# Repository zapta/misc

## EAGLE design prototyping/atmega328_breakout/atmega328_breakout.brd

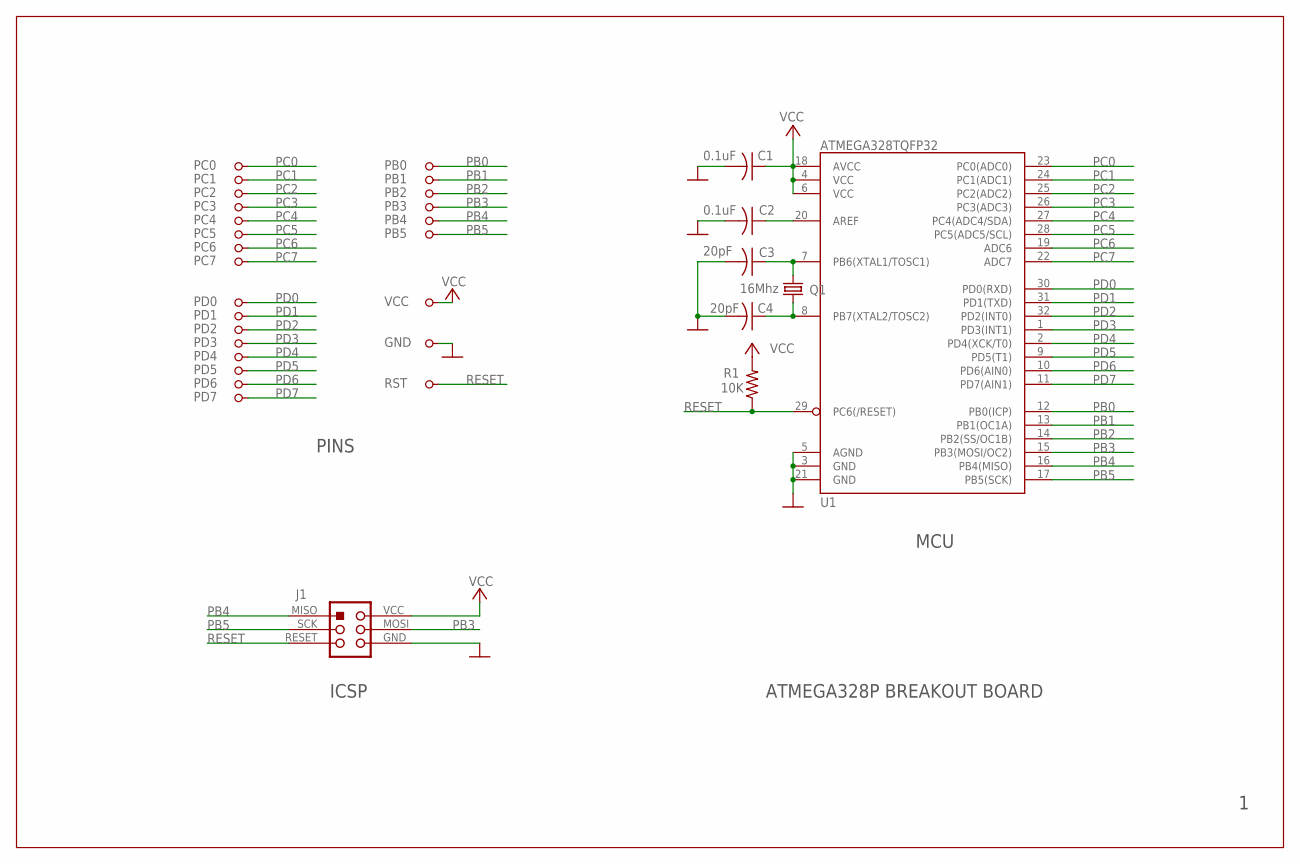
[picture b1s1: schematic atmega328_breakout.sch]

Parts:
C1, C2: 0.1uF; C0603
C3, C4: 20pF; C0603
GND: PINHD-1X1; 1X01
J1: ICSP
PB0, PB1, PB2, PB3, PB4, PB5: PINHD-1X1; 1X01
PC0, PC1, PC2, PC3, PC4, PC5, PC6, PC7: PINHD-1X1; 1X01
PD0, PD1, PD2, PD3, PD4, PD5, PD6, PD7: PINHD-1X1; 1X01
Q1: 16Mhz; CRYSTAL-CTS406
R1: 10K; R0603
RST: PINHD-1X1; 1X01
U1: ATMEGA328TQFP32; TQFP32-08
VCC: PINHD-1X1; 1X01

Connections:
AREF: C2.1, U1.20 (AREF)
GND: C1.2, C2.2, C3.2, C4.2, GND.1, J1.GND, U1.3 (GND), U1.5 (AGND), U1.21 (GND)
unnamed: C3.1, Q1.1, U1.7 (PB6(XTAL1/TOSC1))
unnamed: C4.1, Q1.3 (2), U1.8 (PB7(XTAL2/TOSC2))
PB0: PB0.1, U1.12 (PB0(ICP))
PB1: PB1.1, U1.13 (PB1(OC1A))
PB2: PB2.1, U1.14 (PB2(SS/OC1B))
PB3: J1.MOSI, PB3.1, U1.15 (PB3(MOSI/OC2))
PB4: J1.MISO, PB4.1, U1.16 (PB4(MISO))
PB5: J1.SCK, PB5.1, U1.17 (PB5(SCK))
PC0: PC0.1, U1.23 (PC0(ADC0))
PC1: PC1.1, U1.24 (PC1(ADC1))
PC2: PC2.1, U1.25 (PC2(ADC2))
PC3: PC3.1, U1.26 (PC3(ADC3))
PC4: PC4.1, U1.27 (PC4(ADC4/SDA))
PC5: PC5.1, U1.28 (PC5(ADC5/SCL))
PC6: PC6.1, U1.19 (ADC6)
PC7: PC7.1, U1.22 (ADC7)
PD0: PD0.1, U1.30 (PD0(RXD))
PD1: PD1.1, U1.31 (PD1(TXD))
PD2: PD2.1, U1.32 (PD2(INT0))
PD3: PD3.1, U1.1 (PD3(INT1))
PD4: PD4.1, U1.2 (PD4(XCK/T0))
PD5: PD5.1, U1.9 (PD5(T1))
PD6: PD6.1, U1.10 (PD6(AIN0))
PD7: PD7.1, U1.11 (PD7(AIN1))
RESET: J1.RESET, R1.1, RST.1, U1.29 (PC6(/RESET))
VCC: C1.1, J1.VCC, R1.2, U1.4 (VCC), U1.6 (VCC), U1.18 (AVCC), VCC.1

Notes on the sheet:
ATMEGA328P BREAKOUT BOARD
ICSP
PINS
MCU

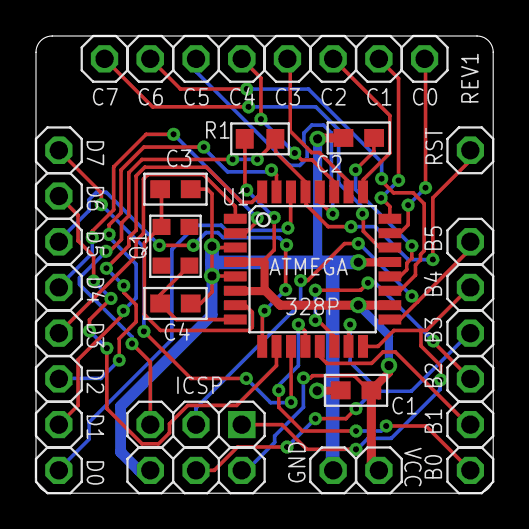
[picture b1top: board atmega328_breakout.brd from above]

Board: 2 copper layers, 25.4 x 25.4 mm, 33 parts (0 on the bottom side), 28 nets.

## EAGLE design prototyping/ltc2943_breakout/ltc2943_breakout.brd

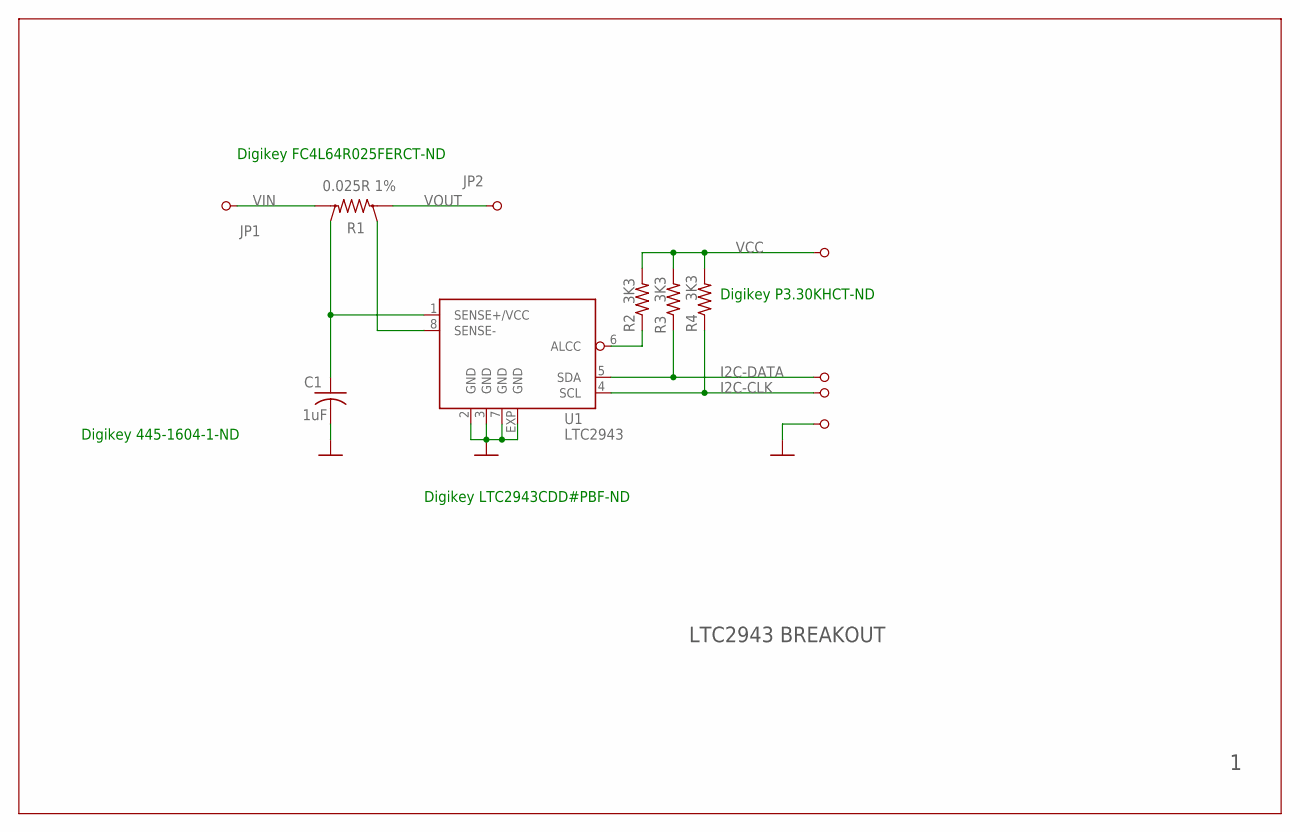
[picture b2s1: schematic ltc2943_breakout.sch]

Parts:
C1: 1uF; C0603
JP1, JP2, JP3, JP4, JP5, JP6: PINHD-1X1; 1X01
R1: 0.025R 1%; KELVIN-6432
R2, R3, R4: 3K3; R0603
U1: LTC2943; DFN8-3X3

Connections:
GND: C1.2, JP6.1, U1.2 (GND), U1.3 (GND), U1.7 (GND), U1.EXP (GND)
I2C-CLK: JP5.1, R4.1, U1.4 (SCL)
I2C-DATA: JP4.1, R3.1, U1.5 (SDA)
unnamed: R2.1, U1.6 (ALCC)
unnamed: R1.V1, U1.8 (SENSE-)
SENSE+: C1.1, R1.V2, U1.1 (SENSE+/VCC)
VCC: JP3.1, R2.2, R3.2, R4.2
VIN: JP1.1, R1.I2
VOUT: JP2.1, R1.I1

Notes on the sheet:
LTC2943 BREAKOUT
Digikey FC4L64R025FERCT-ND
Digikey 445-1604-1-ND
Digikey LTC2943CDD#PBF-ND
Digikey P3.30KHCT-ND

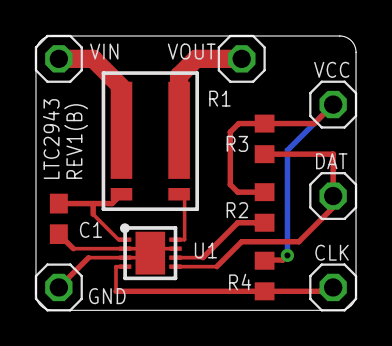
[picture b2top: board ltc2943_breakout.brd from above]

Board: 2 copper layers, 17.8 x 15.2 mm, 12 parts (0 on the bottom side), 9 nets.
